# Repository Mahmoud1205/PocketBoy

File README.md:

# PocketBoy

The PocketBoy is a small handheld console made completely from scratch with a custom PCB and enclosure. The PocketBoy is small enough to fit in a pocket but has a 1000mAh battery for long gaming sessions. The PocketBoy has 8 buttons and a 128x64 monochrome OLED display, it also has a buzzer and a vibration motor.

The PocketBoy is made so you can kill time offline anywhere you are. It is very small (approximately 8x5cm) to easily fit in a pocket and has a strong battery which can be easily replaced. It also has a passive buzzer and vibration motor for extra immersion.

This is a project for the Hack Club Fallout program.

## How to use the PocketBoy

## Fabrication and Assembly Info
- Design files can be found in `/Design/Hardware`.
- Shapr3D link: https://app.shapr3d.com/p/6ae6ebff-efae-4364-8fd7-c0a60253d18e
- Some prototype code can be found in `/Design/Software`. More software will be added in the future.
- M2x20mm screws are used to hold the two enclosure parts together. Please thread them manually after printing the enclosure.
- Please ensure to solder the USB connector accurately so it can fit in the enclosure.
- Please print the design so that the two enclosure parts and all of the buttons are separate from each other.
- The PCB is split into two PCBs, they are connected together using wires after printing both of them. The board connection wires are drawn in the schematic as two 01x01 connectors placed next to each other as in the image below. 
- When soldering the power switch on the bottom PCB, please make sure that its wires come out of the top PCB so the switch can be placed in its position securely.
- After all parts are fabricated, you assemble the console this way: first place the battery at the bottom of the enclosure, then place the bottom PCB above the battery, it should float above the battery because the USB connecter will raise it. Then put the power switch in its hole and secure it in its place. Then place the buttons on the top part of the enclosure and then align the top PCB to be placed above the bottom PCB with a distance enough to keep the buttons stable above the top PCB. Then put the display in the display hole on the top part of the enclosure. Then place both parts of the enclosure on top of each other and hold them together using M2x20mm screws.
- The board can be programmed using an FTDI connector on the top PCB.

## Notes for Fallout reviewers.
As of now there is only a very simple FlappyBird game but I will make more games when the console is built.

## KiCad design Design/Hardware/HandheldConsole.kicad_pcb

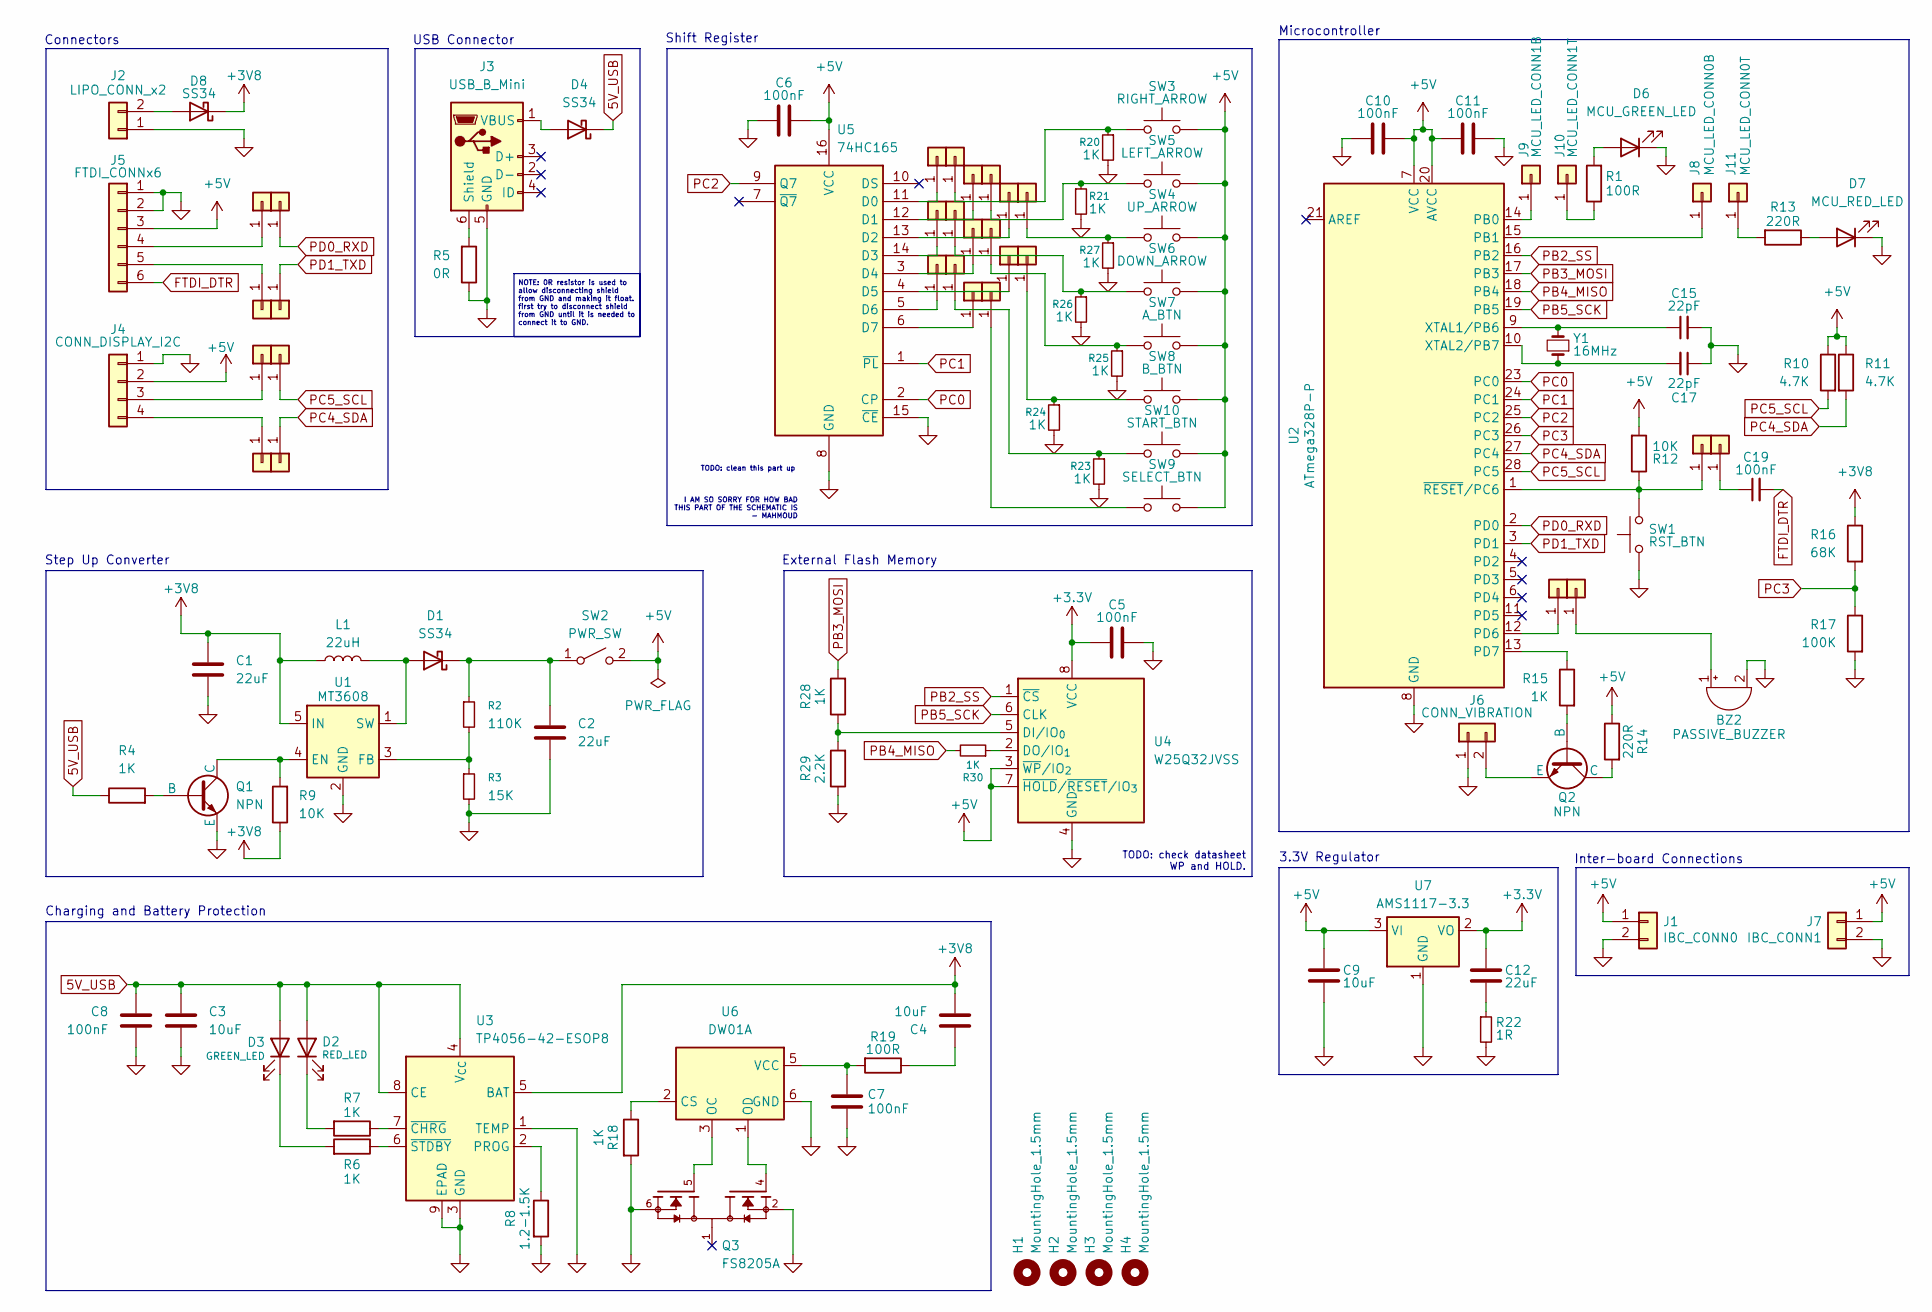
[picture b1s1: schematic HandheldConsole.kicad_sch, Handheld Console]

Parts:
BZ2: PASSIVE_BUZZER; Buzzer_12x9.5RM7.6
C1, C2, C12: 22uF; C_0805_2012Metric
C3, C4, C9: 10uF; C_0805_2012Metric
C5, C6, C7, C8, C10, C11, C19: 100nF; C_0805_2012Metric
C15, C17: 22pF; C_0805_2012Metric
D1, D4, D8: SS34; D_SMA
D2: RED_LED; LED_0805_2012Metric
D3: GREEN_LED; LED_0805_2012Metric
D6: MCU_GREEN_LED; LED_0805_2012Metric
D7: MCU_RED_LED; LED_0805_2012Metric
H1, H2, H3, H4: MountingHole_1.5mm; MountingHole_2.1mm
J1: IBC_CONN0; SolderWire-0.5sqmm_1x02_P4.8mm_D0.9mm_OD2.3mm
J2: LIPO_CONN_x2; SolderWire-0.1sqmm_1x02_P3.6mm_D0.4mm_OD1mm
J3: USB_B_Mini; USB_Mini-B_Wuerth_65100516121_Horizontal
J4: CONN_DISPLAY_I2C; SolderWire-0.1sqmm_1x04_P3.6mm_D0.4mm_OD1mm
J5: FTDI_CONNx6; PinHeader_1x06_P2.54mm_Vertical
J6: CONN_VIBRATION; SolderWire-0.1sqmm_1x02_P3.6mm_D0.4mm_OD1mm
J7: IBC_CONN1; SolderWire-0.5sqmm_1x02_P4.8mm_D0.9mm_OD2.3mm
J8: MCU_LED_CONN0B; SolderWire-0.1sqmm_1x01_D0.4mm_OD1mm
J9: MCU_LED_CONN1B; SolderWire-0.1sqmm_1x01_D0.4mm_OD1mm
J10: MCU_LED_CONN1T; SolderWire-0.1sqmm_1x01_D0.4mm_OD1mm
J11: MCU_LED_CONN0T; SolderWire-0.1sqmm_1x01_D0.4mm_OD1mm
J12, J13, J14, J15, J16, J17, J18, J19, J20, J21, J22, J23, J24, J25, J26, J27, J28, J29, J30, J31, J32, J33, J34, J35, J36, J37, J38, J39: BOTTOM; SolderWire-0.1sqmm_1x01_D0.4mm_OD1mm
L1: 22uH; L_12x12mm_H4.5mm
Q1, Q2: NPN; SOT-23-3
Q3: FS8205A; SOT-23-6; PARTREV 1.7
R1, R19: 100R; R_0805_2012Metric
R2: 110K; R_0805_2012Metric
R3: 15K; R_0805_2012Metric
R4, R6, R7, R15, R18, R20, R21, R23, R24, R25, R26, R27, R28, R30: 1K; R_0805_2012Metric
R5: 0R; R_0805_2012Metric
R8: 1.2-1.5K; R_0805_2012Metric
R9, R12: 10K; R_0805_2012Metric
R10, R11: 4.7K; R_0805_2012Metric
R13, R14: 220R; R_0805_2012Metric
R16: 68K; R_0805_2012Metric
R17: 100K; R_0805_2012Metric
R22: 1R; R_0805_2012Metric
R29: 2.2K; R_0805_2012Metric
SW1: RST_BTN; SW_PUSH_6mm_H4.3mm
SW2: PWR_SW; SolderWire-0.1sqmm_1x02_P3.6mm_D0.4mm_OD1mm
SW3: RIGHT_ARROW; SW_PUSH_1P1T_6x3.5mm_H5.0_APEM_MJTP1250
SW4: UP_ARROW; SW_PUSH_1P1T_6x3.5mm_H5.0_APEM_MJTP1250
SW5: LEFT_ARROW; SW_PUSH_1P1T_6x3.5mm_H5.0_APEM_MJTP1250
SW6: DOWN_ARROW; SW_PUSH_1P1T_6x3.5mm_H5.0_APEM_MJTP1250
SW7: A_BTN; SW_PUSH_1P1T_6x3.5mm_H5.0_APEM_MJTP1250
SW8: B_BTN; SW_PUSH_1P1T_6x3.5mm_H5.0_APEM_MJTP1250
SW9: SELECT_BTN; SW_PUSH_1P1T_6x3.5mm_H5.0_APEM_MJTP1250
SW10: START_BTN; SW_PUSH_1P1T_6x3.5mm_H5.0_APEM_MJTP1250
U1: MT3608; SOT-23-6
U2: ATmega328P-P; DIP-28_W7.62mm
U3: TP4056-42-ESOP8; SOIC-8-1EP_3.9x4.9mm_P1.27mm_EP2.41x3.3mm
U4: W25Q32JVSS; SOIC-8_5.3x5.3mm_P1.27mm
U5: 74HC165; DIP-16_W7.62mm_LongPads
U6: DW01A; SOT-23-6
U7: AMS1117-3.3; SOT-223-3_TabPin2
Y1: 16MHz; Crystal_HC49-4H_Vertical

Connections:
5V_USB: C3.1, C8.1, D2.2 (A), D3.2 (A), D4.1 (K), R4.1, U3.4 (V_{CC}), U3.8 (CE)
+3.3V: C5.2, C12.1, U4.8 (VCC), U7.2 (VO)
+3V8: C1.1, C4.2, D8.1 (K), L1.1, R9.1, R16.1, U1.5 (IN), U3.5 (BAT)
+5V: C6.2, C9.1, C10.2, C11.2, J1.1, J4.2, J5.3, J7.1, R10.1, R11.1, R12.2, R14.1, SW2.2 (B), SW3.1, SW4.2, SW5.2, SW6.2, SW7.2, SW8.2, SW9.2, SW10.2, U2.7 (VCC), U2.20 (AVCC), U4.3 (~WP/IO_{2}), U4.7 (~HOLD/~RESET/IO_{3}), U5.16 (VCC), U7.3 (VI)
FTDI_DTR: C19.2, J5.6
GND: BZ2.2 (-), C1.2, C2.2, C3.2, C5.1, C6.1, C7.2, C8.2, C9.2, C10.1, C11.1, C15.2, C17.1, D6.1 (K), D7.1 (K), J1.2, J2.1, J3.5 (GND), J4.1, J5.1, J5.2, J6.1, J7.2, Q1.3 (E), Q3.2, Q3.3, Q3.6, Q3.7, R3.2, R5.1, R8.2, R17.2, R18.2, R20.2, R21.2, R22.2, R23.2, R24.2, R25.2, R26.2, R27.2, R29.1, SW1.2, U1.2 (GND), U2.8 (GND), U2.22 (GND), U3.1 (TEMP), U3.3 (GND), U3.9 (EPAD), U4.4 (GND), U5.8 (GND), U5.15 (~CE), U6.6 (GND), U7.1 (GND)
unnamed: BZ2.1 (+), J29.1 (Pin_1_1)
unnamed: C4.1, R19.1
unnamed: C12.2, R22.1
unnamed: D1.2 (A), L1.2, U1.1 (SW)
unnamed: C2.1, D1.1 (K), R2.1, SW2.1 (A)
unnamed: D2.1 (K), R7.2
unnamed: D3.1 (K), R6.2
unnamed: D4.2 (A), J3.1 (VBUS)
unnamed: D6.2 (A), R1.2
unnamed: D7.2 (A), R13.1
unnamed: D8.2 (A), J2.2
unnamed: J3.6 (Shield), R5.2
unnamed: J6.2, Q2.3 (E)
unnamed: J8.1 (Pin_1_1), U2.15 (PB1)
unnamed: J9.1 (Pin_1_1), U2.14 (PB0)
unnamed: J10.1 (Pin_1_1), R1.1
unnamed: J11.1 (Pin_1_1), R13.2
unnamed: J12.1 (Pin_1_1), U5.11 (D0)
unnamed: J13.1 (Pin_1_1), R20.1, SW3.2
unnamed: J14.1 (Pin_1_1), U5.12 (D1)
unnamed: J15.1 (Pin_1_1), R21.1, SW5.1
unnamed: J16.1 (Pin_1_1), U5.13 (D2)
unnamed: J17.1 (Pin_1_1), R27.1, SW4.1
unnamed: J18.1 (Pin_1_1), U5.14 (D3)
unnamed: J19.1 (Pin_1_1), R26.1, SW6.1
unnamed: J20.1 (Pin_1_1), U5.3 (D4)
unnamed: J21.1 (Pin_1_1), R25.1, SW7.1
unnamed: J22.1 (Pin_1_1), U5.4 (D5)
unnamed: J23.1 (Pin_1_1), R24.1, SW8.1
unnamed: J24.1 (Pin_1_1), U5.5 (D6)
unnamed: J25.1 (Pin_1_1), R23.1, SW10.1
unnamed: J26.1 (Pin_1_1), U5.6 (D7)
unnamed: J27.1 (Pin_1_1), SW9.1
unnamed: J28.1 (Pin_1_1), U2.12 (PD6)
unnamed: J30.1 (Pin_1_1), R12.1, SW1.1, U2.1 (~RESET/PC6)
unnamed: C19.1, J31.1 (Pin_1_1)
unnamed: J5.4, J32.1 (Pin_1_1)
unnamed: J5.5, J35.1 (Pin_1_1)
unnamed: J4.3, J36.1 (Pin_1_1)
unnamed: J4.4, J39.1 (Pin_1_1)
unnamed: Q1.2 (B), R4.2
unnamed: Q1.1 (C), R9.2, U1.4 (EN)
unnamed: Q2.2 (B), R15.2
unnamed: Q2.1 (C), R14.2
unnamed: R2.2, R3.1, U1.3 (FB)
unnamed: R15.1, U2.13 (PD7)
unnamed: C15.1, U2.9 (XTAL1/PB6), Y1.2
unnamed: C17.2, U2.10 (XTAL2/PB7), Y1.1
unnamed: R8.1, U3.2 (PROG)
unnamed: R7.1, U3.7 (~CHRG)
unnamed: R6.1, U3.6 (~STDBY)
unnamed: R28.1, R29.2, U4.5 (DI/IO_{0})
unnamed: R30.1, U4.2 (DO/IO_{1})
unnamed: R18.1, U6.2 (CS)
unnamed: Q3.5, U6.3 (OC)
unnamed: Q3.4, U6.1 (OD)
unnamed: C7.1, R19.2, U6.5 (VCC)
PB2_SS: U2.16 (PB2), U4.1 (~CS)
PB3_MOSI: R28.2, U2.17 (PB3)
PB4_MISO: R30.2, U2.18 (PB4)
PB5_SCK: U2.19 (PB5), U4.6 (CLK)
PC0: U2.23 (PC0), U5.2 (CP)
PC1: U2.24 (PC1), U5.1 (~PL)
PC2: U2.25 (PC2), U5.9 (Q7)
PC3: R16.2, R17.1, U2.26 (PC3)
PC4_SDA: J38.1 (Pin_1_1), R11.2, U2.27 (PC4)
PC5_SCL: J37.1 (Pin_1_1), R10.2, U2.28 (PC5)
PD0_RXD: J33.1 (Pin_1_1), U2.2 (PD0)
PD1_TXD: J34.1 (Pin_1_1), U2.3 (PD1)

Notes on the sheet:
Step Up Converter
USB Connector
3.3V Regulator
TODO: check datasheet WP and HOLD.
I AM SO SORRY FOR HOW BAD THIS PART OF THE SCHEMATIC IS - MAHMOUD
NOTE: 0R resistor is used to allow disconnecting shield from GND and making it float. first try to disconnect shield from GND until it is needed to connect it to GND.
TODO: clean this part up
Inter-board Connections
Microcontroller
Charging and Battery Protection
Connectors
External Flash Memory
Shift Register

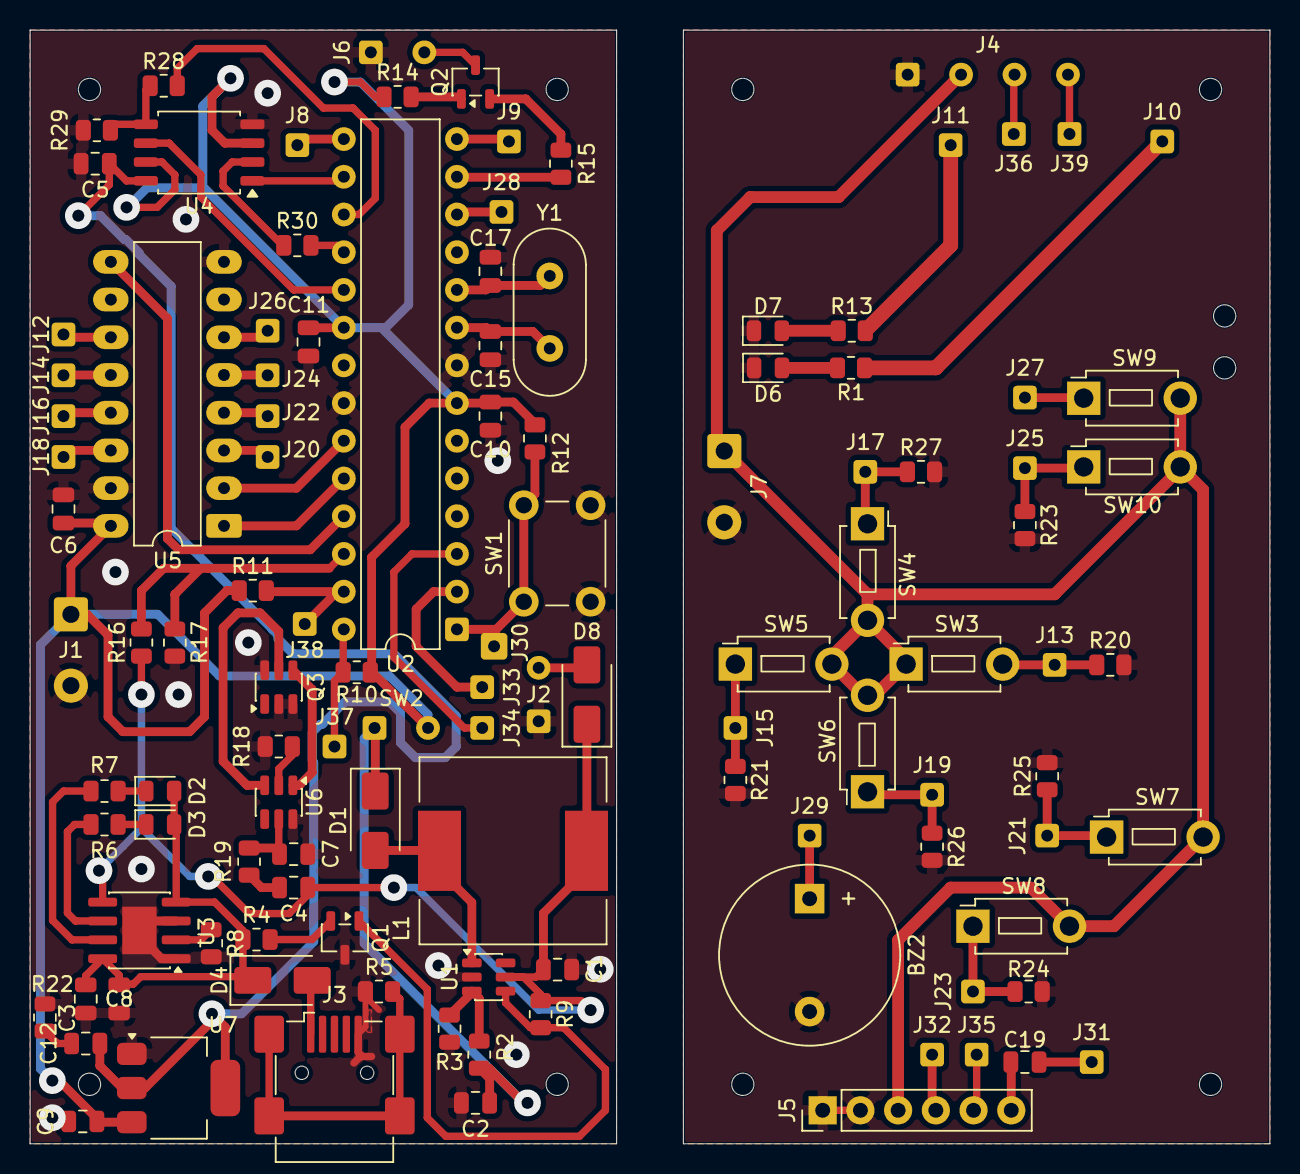
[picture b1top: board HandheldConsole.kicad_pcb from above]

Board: 2 copper layers, 83.5 x 75.0 mm, 124 parts (0 on the bottom side), 75 nets.

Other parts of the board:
H1#2, H2#2, H3#2, H3#3, H3#4, H4#2: MountingHole_1.5mm; MountingHole_2.1mm

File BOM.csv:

"","Sourced","Placed","References","Value","Footprint","Quantity"
1,"","","C5, C6, C7, C8, C10, C11, C19","100nF","C_0805_2012Metric",7
2,"","","C1, C2, C12","22uF","C_0805_2012Metric",3
3,"","","C3, C4, C9","10uF","C_0805_2012Metric",3
4,"","","C15, C17","22pF","C_0805_2012Metric",2
5,"","","R4, R6, R7, R15, R18, R20, R21, R23, R24, R25, R26, R27, R28, R30","1K","R_0805_2012Metric",14
6,"","","R1, R19","100R","R_0805_2012Metric",2
7,"","","R9, R12","10K","R_0805_2012Metric",2
8,"","","R10, R11","4.7K","R_0805_2012Metric",2
9,"","","R13, R14","220R","R_0805_2012Metric",2
10,"","","R2","110K","R_0805_2012Metric",1
11,"","","R3","15K","R_0805_2012Metric",1
12,"","","R5","0R","R_0805_2012Metric",1
13,"","","R8","1.2-1.5K","R_0805_2012Metric",1
14,"","","R16","68K","R_0805_2012Metric",1
15,"","","R17","100K","R_0805_2012Metric",1
16,"","","R22","1R","R_0805_2012Metric",1
17,"","","R29","2.2K","R_0805_2012Metric",1
18,"","","L1","22uH","L_12x12mm_H4.5mm",1
19,"","","D1, D4, D8","SS34","D_SMA",3
20,"","","D2","RED_LED","LED_0805_2012Metric",1
21,"","","D3","GREEN_LED","LED_0805_2012Metric",1
22,"","","D6","MCU_GREEN_LED","LED_0805_2012Metric",1
23,"","","D7","MCU_RED_LED","LED_0805_2012Metric",1
24,"","","U1","MT3608","SOT-23-6",1
25,"","","U2","ATmega328P-P","DIP-28_W7.62mm",1
26,"","","U3","TP4056-42-ESOP8","SOIC-8-1EP_3.9x4.9mm_P1.27mm_EP2.41x3.3mm",1
27,"","","U4","W25Q32JVSS","SOIC-8_5.3x5.3mm_P1.27mm",1
28,"","","U5","74HC165","DIP-16_W7.62mm_LongPads",1
29,"","","U6","DW01A","SOT-23-6",1
30,"","","U7","AMS1117-3.3","SOT-223-3_TabPin2",1
31,"","","Y1","16MHz","Crystal_HC49-4H_Vertical",1
32,"","","SW1","RST_BTN","SW_PUSH_6mm_H4.3mm",1
33,"","","SW2","PWR_SW","SolderWire-0.1sqmm_1x02_P3.6mm_D0.4mm_OD1mm",1
34,"","","SW3","RIGHT_ARROW","SW_PUSH_1P1T_6x3.5mm_H5.0_APEM_MJTP1250",1
35,"","","SW4","UP_ARROW","SW_PUSH_1P1T_6x3.5mm_H5.0_APEM_MJTP1250",1
36,"","","SW5","LEFT_ARROW","SW_PUSH_1P1T_6x3.5mm_H5.0_APEM_MJTP1250",1
37,"","","SW6","DOWN_ARROW","SW_PUSH_1P1T_6x3.5mm_H5.0_APEM_MJTP1250",1
38,"","","SW7","A_BTN","SW_PUSH_1P1T_6x3.5mm_H5.0_APEM_MJTP1250",1
39,"","","SW8","B_BTN","SW_PUSH_1P1T_6x3.5mm_H5.0_APEM_MJTP1250",1
40,"","","SW9","SELECT_BTN","SW_PUSH_1P1T_6x3.5mm_H5.0_APEM_MJTP1250",1
41,"","","SW10","START_BTN","SW_PUSH_1P1T_6x3.5mm_H5.0_APEM_MJTP1250",1
42,"","","Q1, Q2","NPN","SOT-23-3",2
43,"","","BZ2","PASSIVE_BUZZER","Buzzer_12x9.5RM7.6",1
44,"","","Q3","FS8205A","SOT-23-6",1
45,"","","J12, J13, J14, J15, J16, J17, J18, J19, J20, J21, J22, J23, J24, J25, J26, J27, J28, J29, J30, J31, J32, J33, J34, J35, J36, J37, J38, J39","BOTTOM","SolderWire-0.1sqmm_1x01_D0.4mm_OD1mm",28
46,"","","J1","IBC_CONN0","SolderWire-0.5sqmm_1x02_P4.8mm_D0.9mm_OD2.3mm",1
47,"","","J2","LIPO_CONN_x2","SolderWire-0.1sqmm_1x02_P3.6mm_D0.4mm_OD1mm",1
48,"","","J3","USB_B_Mini","USB_Mini-B_Wuerth_65100516121_Horizontal",1
49,"","","J4","CONN_DISPLAY_I2C","SolderWire-0.1sqmm_1x04_P3.6mm_D0.4mm_OD1mm",1
50,"","","J5","FTDI_CONNx6","PinHeader_1x06_P2.54mm_Vertical",1
51,"","","J6","CONN_VIBRATION","SolderWire-0.1sqmm_1x02_P3.6mm_D0.4mm_OD1mm",1
52,"","","J7","IBC_CONN1","SolderWire-0.5sqmm_1x02_P4.8mm_D0.9mm_OD2.3mm",1
53,"","","J8","MCU_LED_CONN0B","SolderWire-0.1sqmm_1x01_D0.4mm_OD1mm",1
54,"","","J9","MCU_LED_CONN1B","SolderWire-0.1sqmm_1x01_D0.4mm_OD1mm",1
55,"","","J10","MCU_LED_CONN1T","SolderWire-0.1sqmm_1x01_D0.4mm_OD1mm",1
56,"","","J11","MCU_LED_CONN0T","SolderWire-0.1sqmm_1x01_D0.4mm_OD1mm",1

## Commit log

2026-05-21 updatea name
2026-05-22 add bom
2026-05-22 add readme
2026-05-22 finalize repo for fallout
2026-05-22 update description
2026-05-22 add more info
2026-05-22 add links to bom
2026-06-02 update zine
2026-06-06 add shapr3d link to readme
